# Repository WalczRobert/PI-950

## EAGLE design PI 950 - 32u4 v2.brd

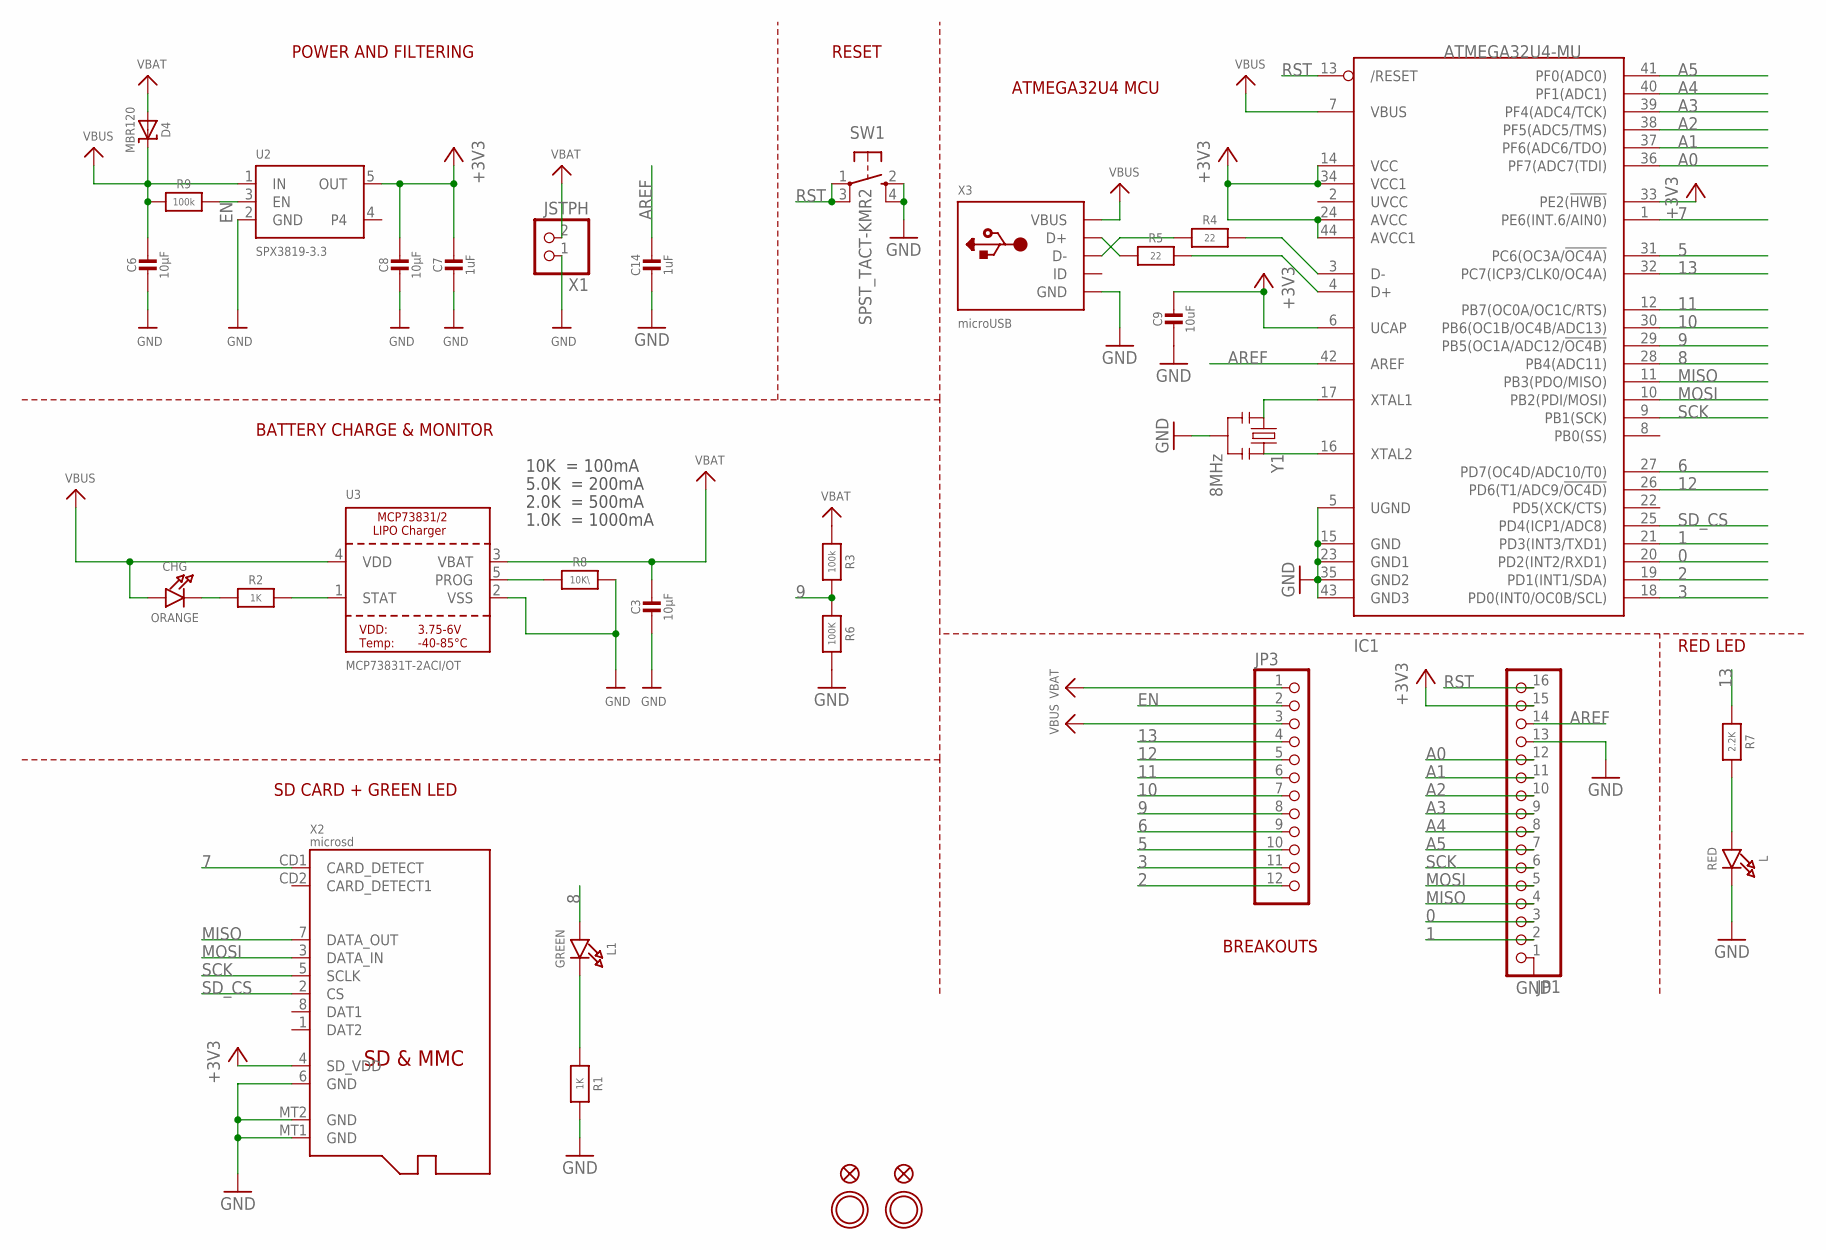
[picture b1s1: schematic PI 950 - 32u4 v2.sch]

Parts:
C3, C6, C8: 10µF; 0805-NO
C7, C14: 1uF; 0603-NO
C9: 10uF; 0805-NO
CHG: ORANGE; CHIPLED_0805_NOOUTLINE
D4: MBR120; SOD-123
IC1: ATMEGA32U4-MU; TQFN44_7MM
JP1: HEADER-1X16ROUND; 1X16_ROUND
JP3: HEADER-1X12; 1X12_ROUND
L: RED; CHIPLED_0805_NOOUTLINE
L1: GREEN; CHIPLED_0805_NOOUTLINE
R1, R2: 1K; 0603-NO
R3, R9: 100k; 0603-NO
R4, R5: 22; 0603-NO
R6: 100K; _0603MP
R7: 2.2K; 0603-NO
R8: 10K\; 0603-NO
SW1: SPST_TACT-KMR2; KMR2
U2: SPX3819-3.3; SOT23-5
U3: MCP73831T-2ACI/OT; SOT23-5
U$31, U$32: MOUNTINGHOLE2.5; MOUNTINGHOLE_2.5_PLATED
U$34, U$35: FIDUCIAL""; FIDUCIAL_1MM
X1: JSTPH; JSTPH2
X2: microsd; MICROSD
X3: microUSB; 4UCONN_20329_V2
Y1: 8MHz; RESONATOR-SMD

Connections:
0: IC1.20 (PD2(INT2/RXD1)), JP1.3
1: IC1.21 (PD3(INT3/TXD1)), JP1.2
2: IC1.19 (PD1(INT1/SDA)), JP3.12
3: IC1.18 (PD0(INT0/OC0B/SCL)), JP3.11
5: IC1.31 (PC6(OC3A/!OC4A)), JP3.10
6: IC1.27 (PD7(OC4D/ADC10/T0)), JP3.9
7: IC1.1 (PE6(INT.6/AIN0)), X2.CD1 (CARD_DETECT)
8: IC1.28 (PB4(ADC11)), L1.A
9: IC1.29 (PB5(OC1A/ADC12/!OC4B)), JP3.8, R3.2, R6.1
10: IC1.30 (PB6(OC1B/OC4B/ADC13)), JP3.7
11: IC1.12 (PB7(OC0A/OC1C/RTS)), JP3.6
12: IC1.26 (PD6(T1/ADC9/!OC4D)), JP3.5
13: IC1.32 (PC7(ICP3/CLK0/OC4A)), JP3.4, R7.1
+3V3: C7.1, C8.1, C9.1, IC1.6 (UCAP), IC1.14 (VCC), IC1.24 (AVCC), IC1.33 (PE2(!HWB)), IC1.34 (VCC1), IC1.44 (AVCC1), JP1.15, U2.5 (OUT), X2.4 (SD_VDD)
A0: IC1.36 (PF7(ADC7(TDI)), JP1.12
A1: IC1.37 (PF6(ADC6/TDO)), JP1.11
A2: IC1.38 (PF5(ADC5/TMS)), JP1.10
A3: IC1.39 (PF4(ADC4/TCK)), JP1.9
A4: IC1.40 (PF1(ADC1)), JP1.8
A5: IC1.41 (PF0(ADC0)), JP1.7
AREF: C14.1, IC1.42 (AREF), JP1.14
D+: IC1.4 (D+), R5.2
D-: IC1.3 (D-), R4.2
EN: JP3.2, R9.2, U2.3 (EN)
GND: C3.2, C6.2, C7.2, C8.2, C9.2, C14.2, IC1.5 (UGND), IC1.15 (GND), IC1.23 (GND1), IC1.35 (GND2), IC1.43 (GND3), JP1.1, JP1.13, L.C, R1.2, R6.2, R8.2, SW1.2 (S), SW1.4 (S1), U2.2 (GND), U3.2 (VSS), X1.1, X2.6 (GND), X2.MT1 (GND), X2.MT2 (GND), X3.BASE@1 (GND), X3.BASE@2 (GND), X3.GND, X3.SPRT@1 (GND), X3.SPRT@2 (GND), X3.SPRT@3 (GND), X3.SPRT@4 (GND), Y1.2
MISO: IC1.11 (PB3(PDO/MISO)), JP1.4, X2.7 (DATA_OUT)
MOSI: IC1.10 (PB2(PDI/MOSI)), JP1.5, X2.3 (DATA_IN)
unnamed: CHG.C, R2.1
unnamed: L.A, R7.2
unnamed: R2.2, U3.1 (STAT)
unnamed: R8.1, U3.5 (PROG)
unnamed: L1.C, R1.1
unnamed: IC1.16 (XTAL2), Y1.3
unnamed: IC1.17 (XTAL1), Y1.1
unnamed: R5.1, X3.D+
unnamed: R4.1, X3.D-
RST: IC1.13 (/RESET), JP1.16, SW1.1, SW1.3 (P1)
SCK: IC1.9 (PB1(SCK)), JP1.6, X2.5 (SCLK)
SD_CS: IC1.25 (PD4(ICP1/ADC8)), X2.2 (CS)
VBAT: C3.1, D4.A, JP3.1, R3.1, U3.3 (VBAT), X1.2
VBUS: C6.1, CHG.A, D4.C, IC1.7 (VBUS), JP3.3, R9.1, U2.1 (IN), U3.4 (VDD), X3.VBUS

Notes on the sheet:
POWER AND FILTERING
RESET
ATMEGA32U4 MCU
10K = 100mA
5.0K = 200mA
2.0K = 500mA
1.0K = 1000mA
BATTERY CHARGE & MONITOR
RED LED
BREAKOUTS
SD CARD + GREEN LED

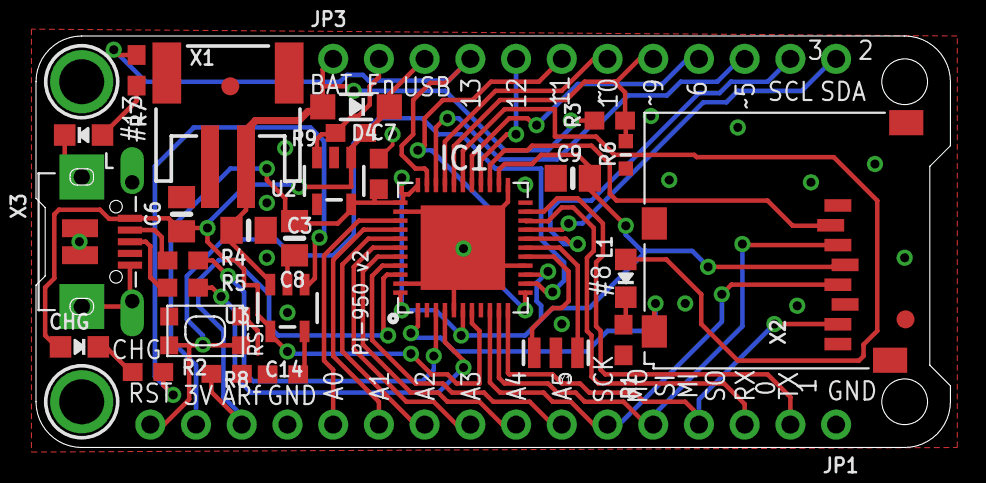
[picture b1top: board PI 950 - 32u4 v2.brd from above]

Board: 2 copper layers, 50.8 x 22.9 mm, 33 parts (0 on the bottom side), 41 nets.

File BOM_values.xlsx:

Qty | Value | Device | Parts | Library | Description | BOM | MANUFACTURER PART NO
1 | ATMEGA32U4-MU | ATMEGA32U4-MU | IC1 |  | http://www.ladyada.net/library/eagle |  | ATMEGA32U4-MU
2 | 1uF | CAP_CERAMIC0603_NO | C7; C14 |  | Ceramic Capacitors |  | 0603ZD105KAT2A
1 | 10uF | CAP_CERAMIC0805-NOOUTLINE | C9,C3; C6; C8 |  | Ceramic Capacitors |  | C0805C106M8RACAUTO
1 | JSTPH | CON_JST_PH_2PIN | X1 |  | JST 2-Pin Right-Angle Connector |  | S2B-PH-SM4-TB(LF)(SN)
1 | MBR120 | DIODE-SCHOTTKYSOD-123 | D4 |  |  |  | MBR120VLSFT1G
2 | FIDUCIAL" | FIDUCIAL" | U$34; U$35 |  | Fiducial Alignment Points | EXCLUDE
1 |  | HEADER-1X12 | JP3 |  |  |  | PH1-13-UA
1 |  | HEADER-1X16ROUND | JP1 |  | PIN HEADER |  | PH1-16-UA
1 | GREEN | LED0805_NOOUTLINE | L1 |  | LED |  | 599-0181-007F
1 | ORANGE | LED0805_NOOUTLINE | CHG |  | LED |  | 599-0130-007F
1 | RED | LED0805_NOOUTLINE | L |  | LED |  | 599-0110-007F
1 | MCP73831T-2ACI/OT | MCP73831/2 | U3 |  | MCP73831/2 LIPO Charger |  | MCP73831T-2DCI/OT
1 | microsd | MICROSD | X2 |  | MicroSD/Transflash Card Holder with SPI pinout |  | 693071010811 | Würth Elektronik
2 | MOUNTINGHOLE2.5 | MOUNTINGHOLE2.5 | U$31; U$32 |  | Mounting Hole | EXCLUDE
1 | 100K | RESISTOR_0603MP | R6;R3; R9 |  | Resistors |  | CR0603-JW-104ELF
1 | 10K | RESISTOR_0603_NOOUT | R8 |  | Resistors |  | ERJ-3GEYJ103V
2 | 1K | RESISTOR_0603_NOOUT | R1; R2 |  | Resistors |  | ERJ-3GEYJ102V
1 | 2.2K | RESISTOR_0603_NOOUT | R7 |  | Resistors |  | ERJ-3GEYJ222V
2 | 22 ohms | RESISTOR_0603_NOOUT | R4; R5 |  | Resistors |  | ERJ-3EKF22R0V
1 | 8MHz | RESONATORSMD | Y1 | SparkFun | Resonator |  | CSTNE8M00G550000R0 | Murata Electronics
1 | SPST_TACT-KMR2 | SPST_TACT-KMR2 | SW1 | adafruit | SMT 6mm switch; EVQQ2 series |  | KMR221GLFS
1 | microUSB | USB_MICRO_20329_V2 | X3 |  | USB Connectors |  | ZX62D-B-5PA8(30)
1 | SPX3819-3.3 | VREG_SOT23-5 | U2 |  | SOT23-5 Fixed Voltage Regulators |  | SPX3819M5-L-3-3/TR

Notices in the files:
parts and their libraries:
microbuilder: This work is placed in the public domain, and may be freely used for commercial and non-commercial work with the following conditions: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
SparkFun: Licensing: CC v3.0 Share-Alike You are welcome to use this library for commercial purposes.
